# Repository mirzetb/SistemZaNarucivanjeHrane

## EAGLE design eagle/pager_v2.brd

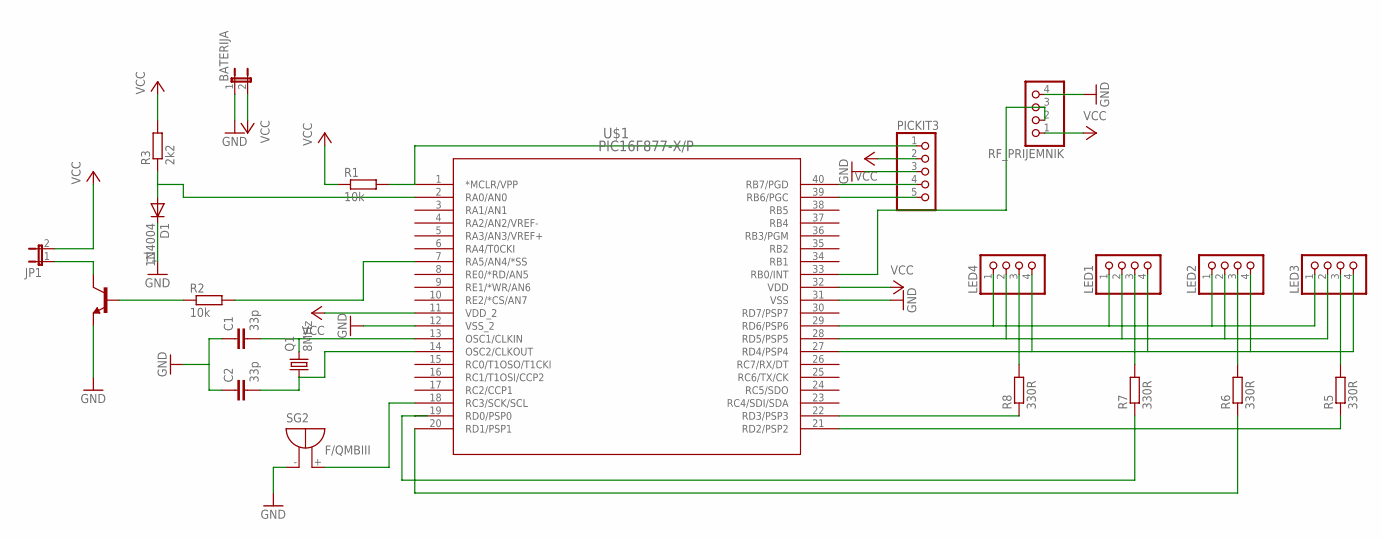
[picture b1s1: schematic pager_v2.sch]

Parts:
BATERIJA: JP1E; JP1
C1, C2: 33p; C025-024X044
D1: 1N4004; DO41-10
JP1: JP1E; JP1
LED1, LED2, LED3, LED4: PINHD-1X4; 1X04
PICKIT3: PINHD-1X5; 1X05
Q1: 8MHz; HC49/S
R1, R2: 10k; 0207/10
R3: 2k2; 0207/10
R5, R6, R7, R8: 330R; 0207/10
RF_PRIJEMNIK: PINHD-1X4; 1X04
SG2: F/QMBIII
T1: -NPN-TO92-EBC; TO92-EBC
U$1: PIC16F877-X/P; PDIP40_600MC

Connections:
GND: BATERIJA.1, C1.1, C2.1, D1.C, PICKIT3.3, RF_PRIJEMNIK.4, SG2.- (+), T1.E, U$1.12 (VSS_2), U$1.31 (VSS)
unnamed: C1.2, Q1.2, U$1.13 (OSC1/CLKIN)
unnamed: LED4.3, R8.2
unnamed: C2.2, Q1.1, U$1.14 (OSC2/CLKOUT)
unnamed: PICKIT3.1, R1.2, U$1.1 (*MCLR/VPP)
unnamed: LED2.3, R6.2
unnamed: R2.1, T1.B
unnamed: JP1.1, T1.C
unnamed: SG2.+ (-), U$1.18 (RC3/SCK/SCL)
unnamed: RF_PRIJEMNIK.2, RF_PRIJEMNIK.3, U$1.33 (RB0/INT)
unnamed: LED3.3, R5.2
unnamed: LED1.3, R7.2
unnamed: LED1.2, LED2.2, LED3.2, LED4.2, U$1.28 (RD5/PSP5)
unnamed: R7.1, U$1.19 (RD0/PSP0)
unnamed: R6.1, U$1.20 (RD1/PSP1)
unnamed: R8.1, U$1.22 (RD3/PSP3)
unnamed: R5.1, U$1.21 (RD2/PSP2)
unnamed: LED1.4, LED2.4, LED3.4, LED4.4, U$1.27 (RD4/PSP4)
unnamed: R2.2, U$1.7 (RA5/AN4/*SS)
unnamed: LED1.1, LED2.1, LED3.1, LED4.1, U$1.29 (RD6/PSP6)
unnamed: PICKIT3.4, U$1.40 (RB7/PGD)
unnamed: PICKIT3.5, U$1.39 (RB6/PGC)
unnamed: D1.A, R3.1, U$1.2 (RA0/AN0)
VCC: BATERIJA.2, JP1.2, PICKIT3.2, R1.1, R3.2, RF_PRIJEMNIK.1, U$1.11 (VDD_2), U$1.32 (VDD)

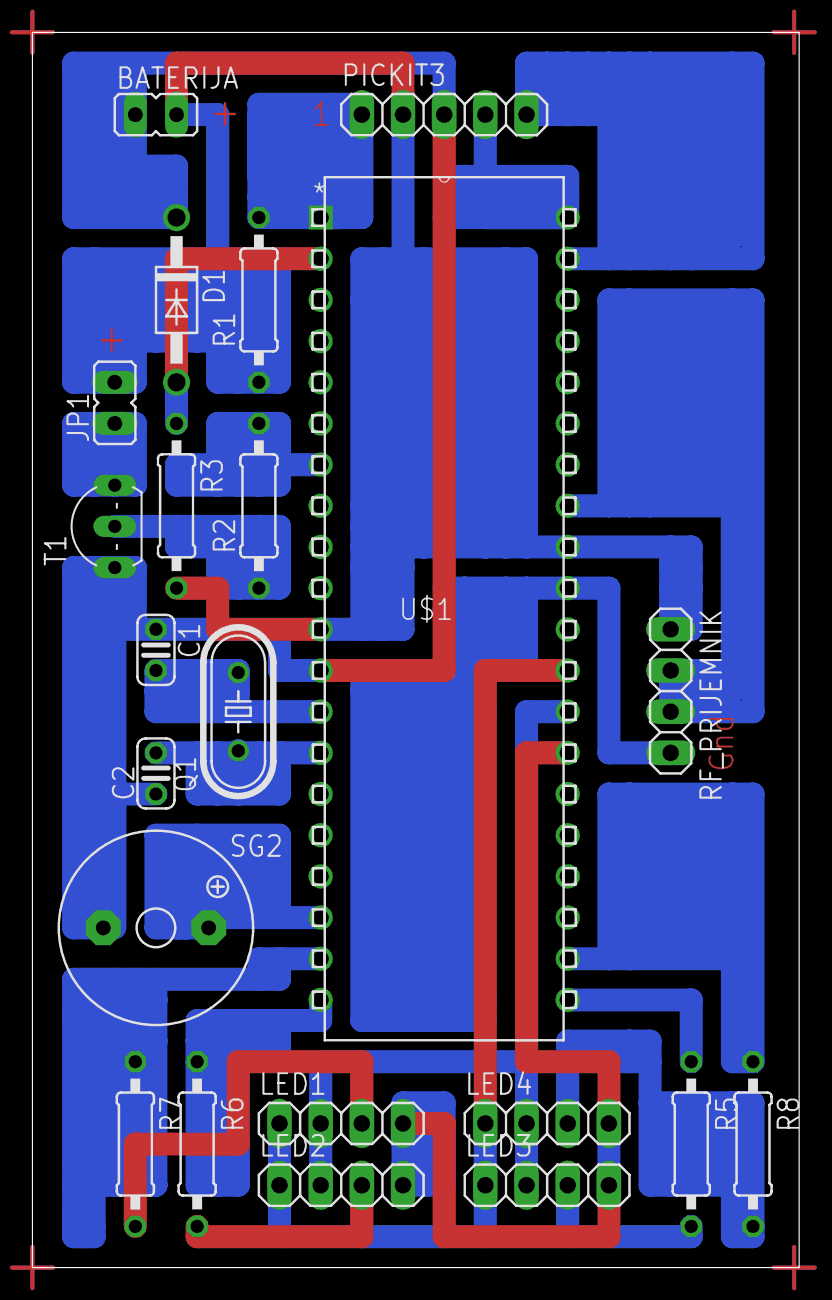
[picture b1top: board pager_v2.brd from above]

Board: 2 copper layers, 47.3 x 76.2 mm, 22 parts (0 on the bottom side), 24 nets.

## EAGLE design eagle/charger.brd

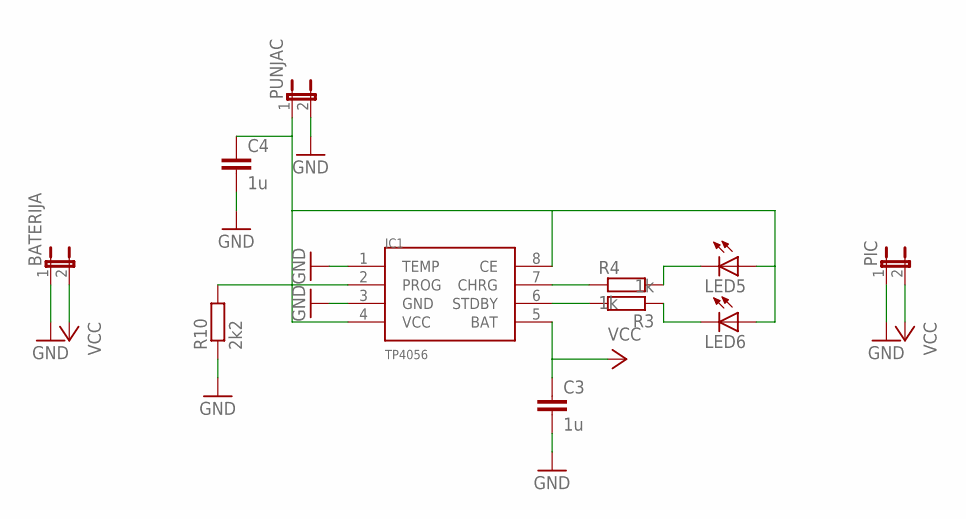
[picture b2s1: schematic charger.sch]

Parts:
BATERIJA: JP1E; JP1
C3, C4: 1u; C050-024X044
IC1: TP4056; SOP-8
LED5, LED6: LED3MM
PIC: JP1E; JP1
PUNJAC: JP1E; JP1
R3, R4: 1k; 0207/10
R10: 2k2; 0207/10

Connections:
GND: BATERIJA.1, C3.2, C4.2, IC1.1 (TEMP), IC1.3 (GND), PIC.1, PUNJAC.2, R10.1
unnamed: IC1.7 (CHRG), R4.1
unnamed: IC1.6 (STDBY), R3.2
unnamed: LED5.K (C), R4.2
unnamed: LED6.K (C), R3.1
unnamed: IC1.2 (PROG), R10.2
unnamed: C4.1, IC1.4 (VCC), IC1.8 (CE), LED5.A, LED6.A, PUNJAC.1
VCC: BATERIJA.2, C3.1, IC1.5 (BAT), PIC.2

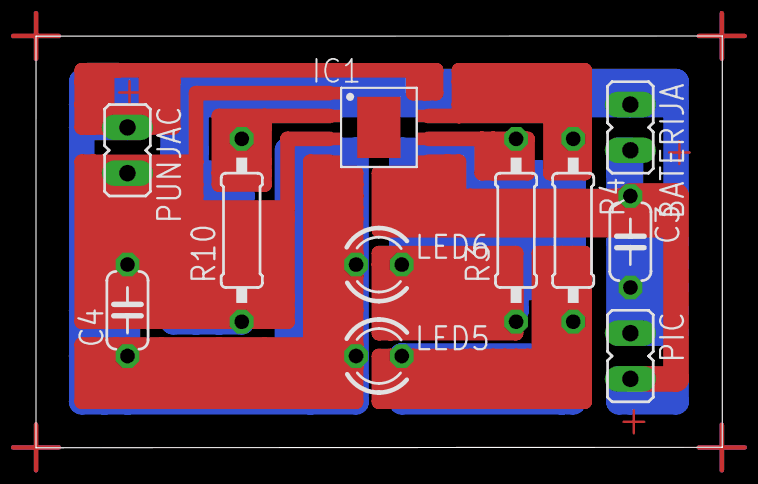
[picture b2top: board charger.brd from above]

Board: 2 copper layers, 38.1 x 22.9 mm, 11 parts (0 on the bottom side), 8 nets.

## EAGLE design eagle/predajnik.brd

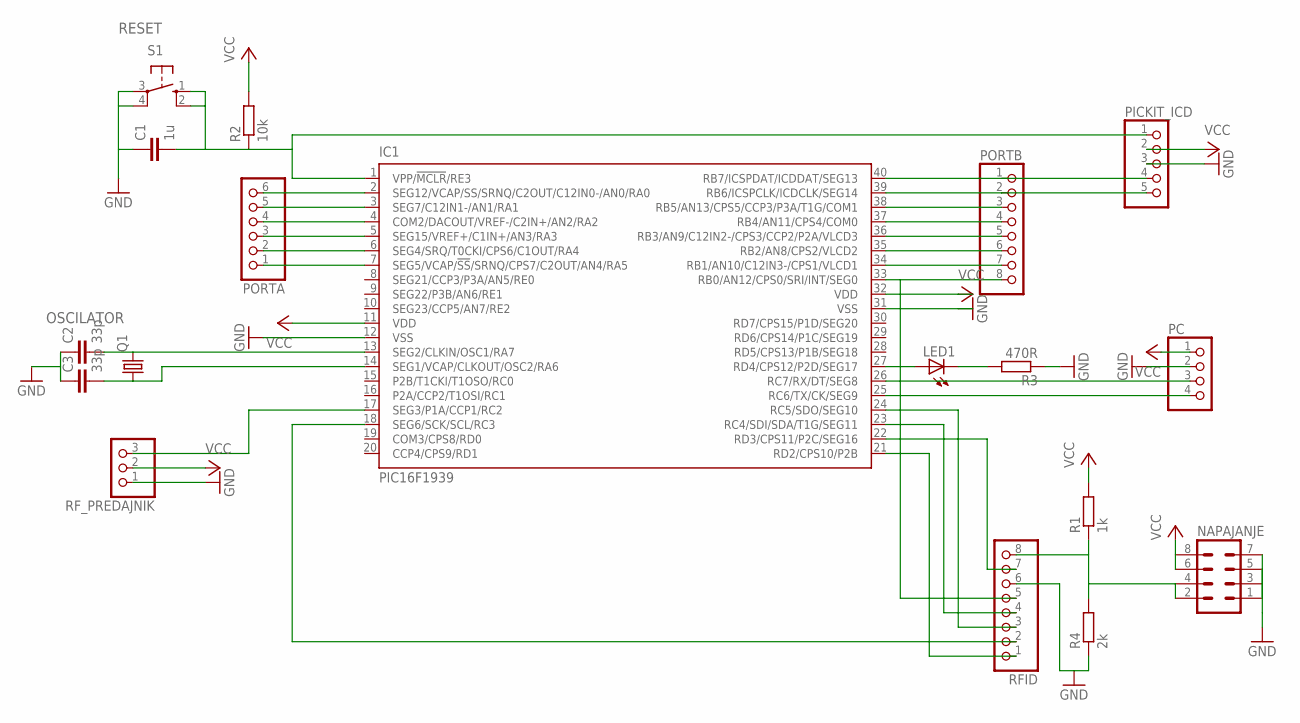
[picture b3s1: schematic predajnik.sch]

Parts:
C1: 1u; C050-024X044
C2, C3: 33p; C025-024X044
IC1: PIC16F1939; DIL40
LED1: LED5MM
NAPAJANJE: MA04-2
PC: PINHD-1X4; 1X04
PICKIT_ICD: PINHD-1X5; 1X05
PORTA: PINHD-1X6; 1X06
PORTB: PINHD-1X8; 1X08
Q1: CRYSTALHC49S; HC49/S
R1: 1k; 0207/10
R2: 10k; 0207/10
R3: 470R; 0207/10
R4: 2k; 0207/10
RFID: PINHD-1X8; 1X08
RF_PREDAJNIK: PINHD-1X3; 1X03
S1: 10-XX; B3F-10XX

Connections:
GND: C1.1, C2.1, C3.1, IC1.12 (VSS), IC1.31 (VSS), NAPAJANJE.1, NAPAJANJE.3, NAPAJANJE.5, NAPAJANJE.7, PC.2, PICKIT_ICD.3, R3.1, R4.1, RFID.6, RF_PREDAJNIK.1, S1.3, S1.4 (P1)
unnamed: IC1.22 (RD3/CPS11/P2C/SEG16), RFID.7
unnamed: IC1.17 (SEG3/P1A/CCP1/RC2), RF_PREDAJNIK.3
unnamed: C1.2, IC1.1 (VPP/!MCLR!/RE3), PICKIT_ICD.1, R2.1, S1.1 (S), S1.2 (S1)
unnamed: C3.2, IC1.14 (SEG1/VCAP/CLKOUT/OSC2/RA6), Q1.1
unnamed: C2.2, IC1.13 (SEG2/CLKIN/OSC1/RA7), Q1.2
unnamed: IC1.40 (RB7/ICSPDAT/ICDDAT/SEG13), PICKIT_ICD.4, PORTB.1
unnamed: IC1.39 (RB6/ICSPCLK/ICDCLK/SEG14), PICKIT_ICD.5, PORTB.2
unnamed: IC1.18 (SEG6/SCK/SCL/RC3), RFID.2
unnamed: IC1.24 (RC5/SDO/SEG10), RFID.3
unnamed: IC1.23 (RC4/SDI/SDA/T1G/SEG11), RFID.4
unnamed: IC1.33 (RB0/AN12/CPS0/SRI/INT/SEG0), PORTB.8, RFID.5
unnamed: IC1.21 (RD2/CPS10/P2B), RFID.1
unnamed: IC1.27 (RD4/CPS12/P2D/SEG17), LED1.A
unnamed: IC1.38 (RB5/AN13/CPS5/CCP3/P3A/T1G/COM1), PORTB.3
unnamed: IC1.7 (SEG5/VCAP/!SS!/SRNQ/CPS7/C2OUT/AN4/RA5), PORTA.1
unnamed: IC1.6 (SEG4/SRQ/T0CKI/CPS6/C1OUT/RA4), PORTA.2
unnamed: IC1.5 (SEG15/VREF+/C1IN+/AN3/RA3), PORTA.3
unnamed: IC1.4 (COM2/DACOUT/VREF-/C2IN+/AN2/RA2), PORTA.4
unnamed: IC1.3 (SEG7/C12IN1-/AN1/RA1), PORTA.5
unnamed: IC1.2 (SEG12/VCAP/SS/SRNQ/C2OUT/C12IN0-/AN0/RA0), PORTA.6
unnamed: IC1.37 (RB4/AN11/CPS4/COM0), PORTB.4
unnamed: IC1.36 (RB3/AN9/C12IN2-/CPS3/CCP2/P2A/VLCD3), PORTB.5
unnamed: IC1.35 (RB2/AN8/CPS2/VLCD2), PORTB.6
unnamed: IC1.34 (RB1/AN10/C12IN3-/CPS1/VLCD1), PORTB.7
unnamed: IC1.25 (RC6/TX/CK/SEG9), PC.4
unnamed: IC1.26 (RC7/RX/DT/SEG8), PC.3
unnamed: LED1.K (C), R3.2
unnamed: NAPAJANJE.2, NAPAJANJE.4, R1.1, R4.2, RFID.8
VCC: IC1.11 (VDD), IC1.32 (VDD), NAPAJANJE.6, NAPAJANJE.8, PC.1, PICKIT_ICD.2, R1.2, R2.2, RF_PREDAJNIK.2

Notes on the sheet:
RESET
OSCILATOR

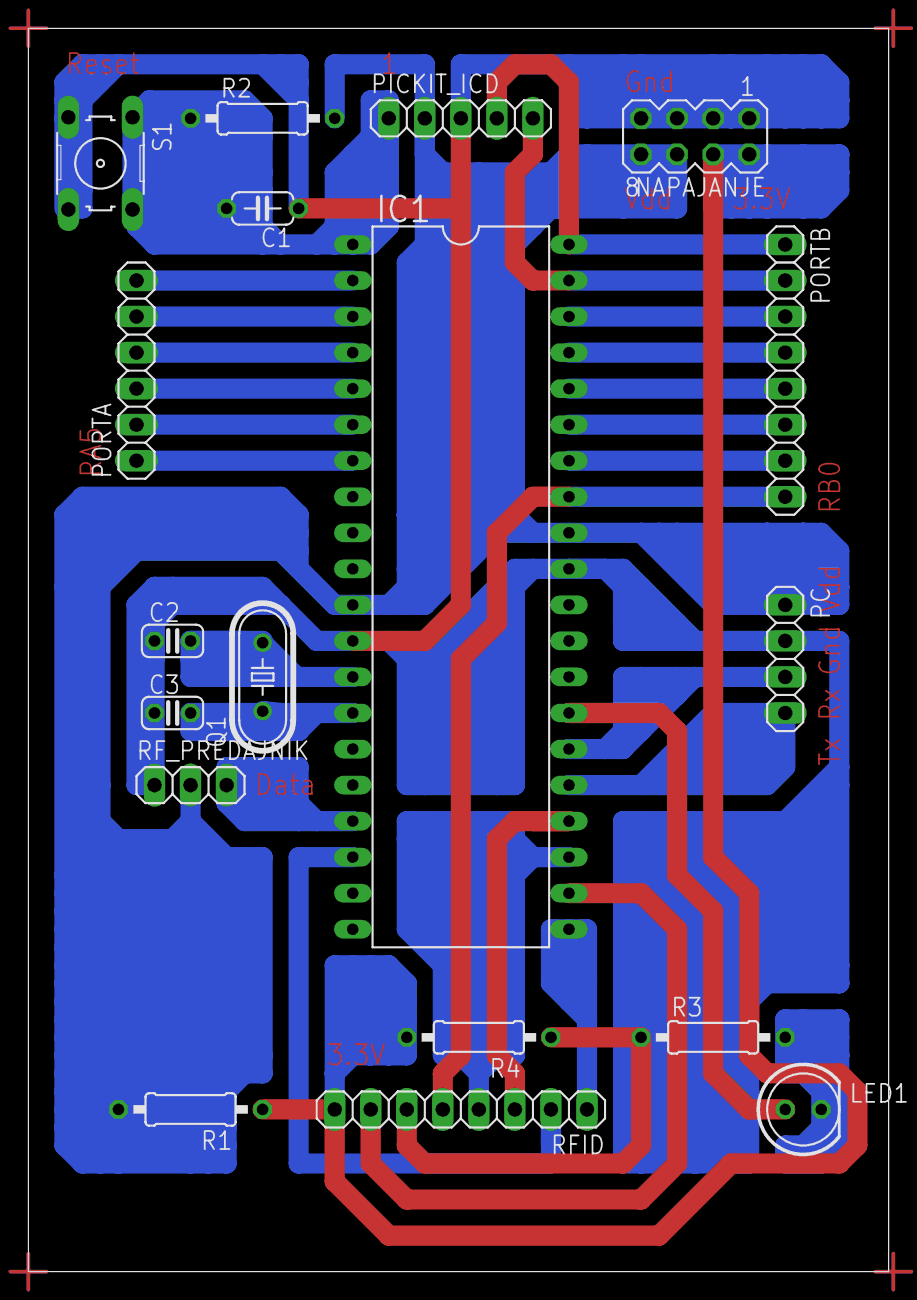
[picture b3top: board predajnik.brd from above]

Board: 2 copper layers, 60.6 x 87.6 mm, 18 parts (0 on the bottom side), 30 nets.

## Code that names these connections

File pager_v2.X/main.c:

/*
 * Embedded solutions and SHIT - Software-Hardware Integration and Testing
 * Elektrotehnicki fakultet Sarajevo
 * Odsjek za automatiku i elektroniku
 * Praktikum automatike
 * 
 * Projektni zadatak: Sistem za narucivanje hrane u restoranu
 * File:    Pager_v2 main.c
 * Authors: Almir Besic
 *          Mirzet Brkic
 *          Semir Berkovic
 */

// PIC16F877A
#include <xc.h>

// CONFIG
#pragma config FOSC = HS        // Oscillator Selection bits (HS oscillator)
#pragma config WDTE = OFF       // Watchdog Timer Enable bit (WDT disabled)
#pragma config PWRTE = OFF      // Power-up Timer Enable bit (PWRT disabled)
#pragma config BOREN = OFF      // Brown-out Reset Enable bit (BOR disabled)
#pragma config LVP = OFF        // Low-Voltage (Single-Supply) In-Circuit Serial Programming Enable bit (RB3 is digital I/O, HV on MCLR must be used for programming)
#pragma config CPD = OFF        // Data EEPROM Memory Code Protection bit (Data EEPROM code protection off)
#pragma config WRT = OFF        // Flash Program Memory Write Enable bits (Write protection off; all program memory may be written to by EECON control)
#pragma config CP = OFF         // Flash Program Memory Code Protection bit (Code protection off)

// Frekvencija oscilatora
#define _XTAL_FREQ 8000000

// Pomocni makroi za pristup bitima varijable
#define testBit(var, bit) ((var) & (1 << (bit)))
#define setBit(var, bit) ((var) |= (1 << (bit)))
#define clrBit(var, bit) ((var) &= ~(1 << (bit)))

// Alijasi za komponente/pinove
#define VIB RA5     // Vibrator
#define BUZZ RC3    // Buzzer
#define DATA RB0    // Data pin RF prijemnika
#define D1 RD0      // Katoda RGB diode 1
#define D2 RD1      // Katoda RGB diode 2
#define D3 RD2      // Katoda RGB diode 3
#define D4 RD3      // Katoda RGB diode 4
#define BLUE RD6    // B pin RGB dioda
#define GREEN RD5   // G pin RGB dioda
#define RED RD4     // R pin RGB dioda
#define BAT RA0     // Napon baterije

// Stanje debuggera/komunikacije sa PC-om
#define DEBUG 1

// Identifikacija pagera
char pagerID = 'K';
char opsegID;
char message_header = 0x00;

// Pomocne vrijable
char play = 0;
char loop = 0;
char i = 0;
char brojacLED = 0;
char brojacVIB = 0;
char sound = 0;
char prazna = 0;
// Stanja pagera
enum {CEKANJE, PROZVAN, IZVANOPSEGA} STANJE;
// Stanja baterije
enum {PRAZNA, NIJEPRAZNA} BATERIJA;
 
// Init metode
void init();
void init_analog();
void init_buzz();
void init_batt();
void init_led();
void init_debug();

// Pmocne metode
void led_show();
void rf_decode();

// Prekidna metoda
void interrupt prekidna_rutina();

void main(void){
    init();
    while(1){
        rf_decode();
    } 
}

// Funkcija za dekodiranje RF signala
void rf_decode() {
    char podatak = 0;
    for (i = 0; i < 100; i++){
        __delay_us(20);
        if (DATA == 0) return;
    }

    while(DATA == 1);
    __delay_us(850);

    for(i = 0; i < 8; i++){
        if(DATA == 1)
            setBit(podatak, i);
        else
            clrBit(podatak, i);
        __delay_us(1000);
    }
    TXREG = podatak;
    
    if(podatak == '*' || podatak == '#'){
        message_header = podatak;
        opsegID = podatak;
        if(STANJE == IZVANOPSEGA){
            STANJE = CEKANJE;
            RED = 0;
            GREEN = 0;
            VIB = 0;
        }
    } else if(podatak == pagerID) {
        if(message_header == '*' && STANJE == CEKANJE || STANJE == IZVANOPSEGA)
            STANJE = PROZVAN;
        
        if(message_header == '#' && STANJE == PROZVAN || STANJE == IZVANOPSEGA) {
            STANJE = CEKANJE;
            RED = 0;
            GREEN = 0;
            VIB = 0;
        }
        message_header = 0x00;
    }
}

void interrupt prekidna_rutina(){
    if (TMR0IE && TMR0IF){
        TMR0IF = 0;
        if(STANJE != CEKANJE && BATERIJA == NIJEPRAZNA){ 
            brojacLED++;
            if(brojacLED == 8){
                play++;
                brojacLED = 0;
                if(STANJE == PROZVAN){
                    GREEN = 1;
                    RED = 0;
                } else if (STANJE == IZVANOPSEGA){
                    RED = 1;
                    GREEN = 0;
                } 
                led_show();
            }
        }
    } else if(TMR2IE && TMR2IF){
        TMR2IF = 0;
        if(STANJE == PROZVAN || STANJE == IZVANOPSEGA && BATERIJA == NIJEPRAZNA) {
            if(play < 2){
                sound++;
                VIB = 0;
                if(sound == 1) BUZZ = 1;
                if (sound == 2){
                    sound = 0;
                    BUZZ = 0;
                }
            } else if(play < 4)
                VIB = 1;
              else
                play = 0;
        }
    } else if (TMR1IE && TMR1IF){
        TMR1IF = 0;
        loop++;
        if (loop == 19){
           if (opsegID == 0x00)
                STANJE = IZVANOPSEGA;
            else 
                opsegID = 0x00;
            loop = 0;
            GO = 1;
        }
    } else if (ADIE && ADIF){
        ADIF = 0;
        if (ADRESH > 55) {
            BATERIJA = PRAZNA;
            RED = 1;
            GREEN = 0;
            D1 = D2 = D3 = D4 = 0;
            prazna = 1;
        } else {
            BATERIJA = NIJEPRAZNA;
            if(prazna == 1){
                D1 = D2 = D3 = D4 = 1;
                RED = 0;
                GREEN = 0;
            }
            prazna = 0;
        }
    }
}

// Inicijalizacija stanja, usmjerenja pinova, pocetnog stanja pinova,
// AD konvertora, timera i prekida
void init() {
    // Pocetno stanje
    STANJE = CEKANJE;
    
    // Pocetno stanje baterije
    BATERIJA = NIJEPRAZNA;
    
    // Usmjerenja pinova
    TRISD = 0x00;           // PORTD je izlazni [RGB diode]
    TRISAbits.TRISA0 = 1;   // RA0 je ulazni [Napon baterije]
    TRISAbits.TRISA5 = 0;   // RA5 je izlazni [Vibrator]
    TRISCbits.TRISC3 = 0;   // RC2 je izlazni [Buzzer]
    TRISBbits.TRISB0 = 1;   // RB0 je ulazni [Data pin RF prijemnika]
    
    // Pocetna stanja pinova
    // Sve diode ugasene, nema boje
    D1 = 1;
    D2 = 1;
    D3 = 1;
    D4 = 1;
    RED = 0;
    GREEN = 0;
    BLUE = 0;
    
    VIB = 0;    // Vibrator iskljucen
    BUZZ = 0;   // Buzzer iskljucen
    
    // Inicijalizacija modula
    init_analog();
    init_buzz();
    init_batt();
    init_led();
    PEIE = 1;
    GIE = 1;
    if (DEBUG == 1)
        init_debug();
}

//  Inicijalizacija AD konvertora
void init_analog() {
    ADFM = 0;   // Lijevo poravnavanje rezultata
   
    PCFG3 = 1;  // RA0 analogni, RA1-7 digitalni
    PCFG2 = 1;  // Vref+ = Vdd, Vref- = Vss
    PCFG1 = 1;
    PCFG0 = 0;
    
    CHS2 = 0;   // Channel 0 (AN0)
    CHS1 = 0;
    CHS0 = 0;

    ADCS2 = 1;  // Interni RC oscilator
    ADCS1 = 1;
    ADCS0 = 1;
    
    ADON = 1;   // Ukljuivanje modula
    ADIE = 1;
}

// Inicijalizacija TIMER2 modula 
void init_buzz() {  
    T2CKPS1 = 1;    // Prescale 1:16
    T2CKPS0 = 1;
    
    PR2 = 125;
    TMR2ON = 1;     // Ukljucivanje Timer 2
    TMR2IE = 1;
}

// Inicijalizacija TIMER1 modula [Indikacija baterije, izlazka iz opsega]
void init_batt() {
    T1CKPS1 = 1; // Prescaler 1:8
    T1CKPS0 = 1;
    
    T1OSCEN = 0;
    TMR1CS = 0;
    
    TMR1ON = 1;
    TMR1IE = 1;
}

// Inicijalizacija Timer 0 modula
void init_led() {
    T0CS = 0;
    
    PSA = 0;    // Prescaler 1:8
    PS2 = 1;
    PS1 = 1;
    PS0 = 1;
    TMR0IE = 1;
}

// Inicijalizacija serijske komunikacije sa PC-om
void init_debug() {
    BRGH = 1;
    SPBRG = 51;
    SYNC = 0;
    SPEN = 1;
    TXEN = 1;
}

// LED rotacija
void led_show() {
    if (D1 == 0) {
        D1 = 1;
        D2 = 0;
    } else if(D2 == 0) {
        D2 = 1;
        D3 = 0;
    } else if(D3 == 0) {
        D3 = 1;
        D4 = 0;
    } else {
        D4 = 1;
        D1 = 0;
    }
}

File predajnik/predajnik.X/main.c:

/*
 * Embedded solutions and SHIT - Software-Hardware Integration and Testing
 * Elektrotehnicki fakultet Sarajevo
 * Odsjek za automatiku i elektroniku
 * Praktikum automatike
 * 
 * Projektni zadatak: Sistem za narucivanje hrane u restoranu
 * File:    Predajnik main.c
 * Authors: Almir Besic
 *          Mirzet Brkic
 *          Semir Berkovic
 */
// PIC16F1939

#include <xc.h>
// CONFIG1
#pragma config FOSC = HS        // Oscillator Selection (HS Oscillator, High-speed crystal/resonator connected between OSC1 and OSC2 pins)
#pragma config WDTE = OFF       // Watchdog Timer Enable (WDT disabled)
#pragma config PWRTE = OFF      // Power-up Timer Enable (PWRT disabled)
#pragma config MCLRE = ON       // MCLR Pin Function Select (MCLR/VPP pin function is MCLR)
#pragma config CP = OFF         // Flash Program Memory Code Protection (Program memory code protection is disabled)
#pragma config CPD = OFF        // Data Memory Code Protection (Data memory code protection is disabled)
#pragma config BOREN = OFF      // Brown-out Reset Enable (Brown-out Reset disabled)
#pragma config CLKOUTEN = OFF   // Clock Out Enable (CLKOUT function is disabled. I/O or oscillator function on the CLKOUT pin)
#pragma config IESO = OFF       // Internal/External Switchover (Internal/External Switchover mode is disabled)
#pragma config FCMEN = OFF      // Fail-Safe Clock Monitor Enable (Fail-Safe Clock Monitor is disabled)

// CONFIG2
#pragma config WRT = OFF        // Flash Memory Self-Write Protection (Write protection off)
#pragma config VCAPEN = OFF     // Voltage Regulator Capacitor Enable (All VCAP pin functionality is disabled)
#pragma config PLLEN = OFF      // PLL Enable (4x PLL disabled)
#pragma config STVREN = OFF     // Stack Overflow/Underflow Reset Enable (Stack Overflow or Underflow will not cause a Reset)
#pragma config BORV = LO        // Brown-out Reset Voltage Selection (Brown-out Reset Voltage (Vbor), low trip point selected.)
#pragma config LVP = OFF        // Low-Voltage Programming Enable (High-voltage on MCLR/VPP must be used for programming)

// Frekvencija oscilatora
#define _XTAL_FREQ 8000000

// Pomocni makroi za pristup bitima varijable
#define testBit(var, bit) ((var) & (1 << (bit)))
#define setBit(var, bit) ((var) |= (1 << (bit)))
#define clrBit(var, bit) ((var) &= ~(1 << (bit)))

// Alijasi za komponente/pinove
#define DATA RC2    // Data pin RF predajnika
#define LED RD4     // Anoda LED 
#define RST RD3     // Reset pin RFID modula
#define IRQ RB0     // Interrupt pin RFID modula
#define SDI RC4     // SDI/MISO pin RFID modula
#define SDO RC5     // SDO/MOSI pin RFID modula
#define SCK RC3     // SCK pin RFID modula
#define SDA RD2     // SDA pin RFID modula

// Pomocne varijable
char t = 0;
char byteNo = 0;
char rf_data[2];
char pcData;
char send = 0;

void interrupt prekidna_rutina();

// Pomocne funkcije
void rf_send();
void init();
void init_serial();
void init_rf();

void main(void) {
    init();
    while(1){
    }
}

void interrupt prekidna_rutina(){
    if(TMR0IE && TMR0IF){
        TMR0 = 6;
        TMR0IF = 0;
        if(send == 1)
            rf_send();
        else t = 0;
    } else if (RCIE && RCIF) {
        pcData = RCREG;
        if(pcData == '*' || pcData == '#') {
            rf_data[0] = pcData;
            send = 0;
        }
        else {
            rf_data[1] = pcData;
            send = 1;
        }
        
    }
}

// Inicijalizacija pinova, RF modula, serijske komunikacije i prekida
void init(){
    TRISCbits.TRISC2 = 0;   // RC2 je izlazni [Data pin RF predajnika]
    DATA = 0;
    
    init_rf();
    init_serial();
    PEIE = 1;
    RCIE = 1;
    GIE = 1;
}

// Inicijalizacija TIMER0 [osnovni takt rf signala]
void init_rf(){
    T0CS = 0;
    T0SE = 1;
    PSA = 0; // PRESCALER 1:4
    PS2 = 0;
    PS1 = 0;
    PS0 = 1;
    TMR0 = 6;
    TMR0IE = 1;
}

// Funkcija za generisanje naponskog nivoa RF signala (manchester enkodiranja)
void rf_send(){
    // "zauzimanje" etera - 10 promjena 0->1->0
    if (t == 0) DATA = 1;
    else if (t < 10) DATA = !DATA;
    else if (t < 16) DATA = 1;   
    else if (t < 17)  DATA = 0;
    else {
        if (t%2 == 1){
            // Signal podatka
            if (testBit(rf_data[byteNo], (t - 17)/2)) DATA = 1;
            else DATA = 0;
        } else {
            // Diferencijalni signal
            if (testBit(rf_data[byteNo], (t - 17)/2)) DATA = 0;
            else DATA = 1;
        }
    }
    t++;
    // Kraj poruke
    if (t == 34){
        DATA = 0;
        t = 0;
        if(byteNo == 0) 
            byteNo = 1;
        else 
            byteNo = 0;
    }
}

// Inicijalizacija serijskog modula
void init_serial() {
    SPEN = 1;
    SYNC = 0;
    BRG16 = 0;
    BRGH = 1;
    SPBRGH = 0x00;
    SPBRGL = 51;
    CREN = 1;
    SREN = 1;
    TXEN = 1;
}

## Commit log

2016-03-06 svi mplab projekti
2016-03-06 organizacija foldera
2016-03-14 dokumentacija
2016-04-09 dodana pc aplikacija
2016-04-09 svasta nesto
2016-06-02 pager done
2016-06-18 sminka
2016-06-18 eagle
2016-06-18 pager_v2.brd
2016-06-27 pager code v2 initial commit'
2016-06-29 code (haman) final
2016-06-30 code final
